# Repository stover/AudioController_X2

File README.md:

# AudioController_X2
RN52 based audio board with ATMega328P and TSOP38238 IR control.

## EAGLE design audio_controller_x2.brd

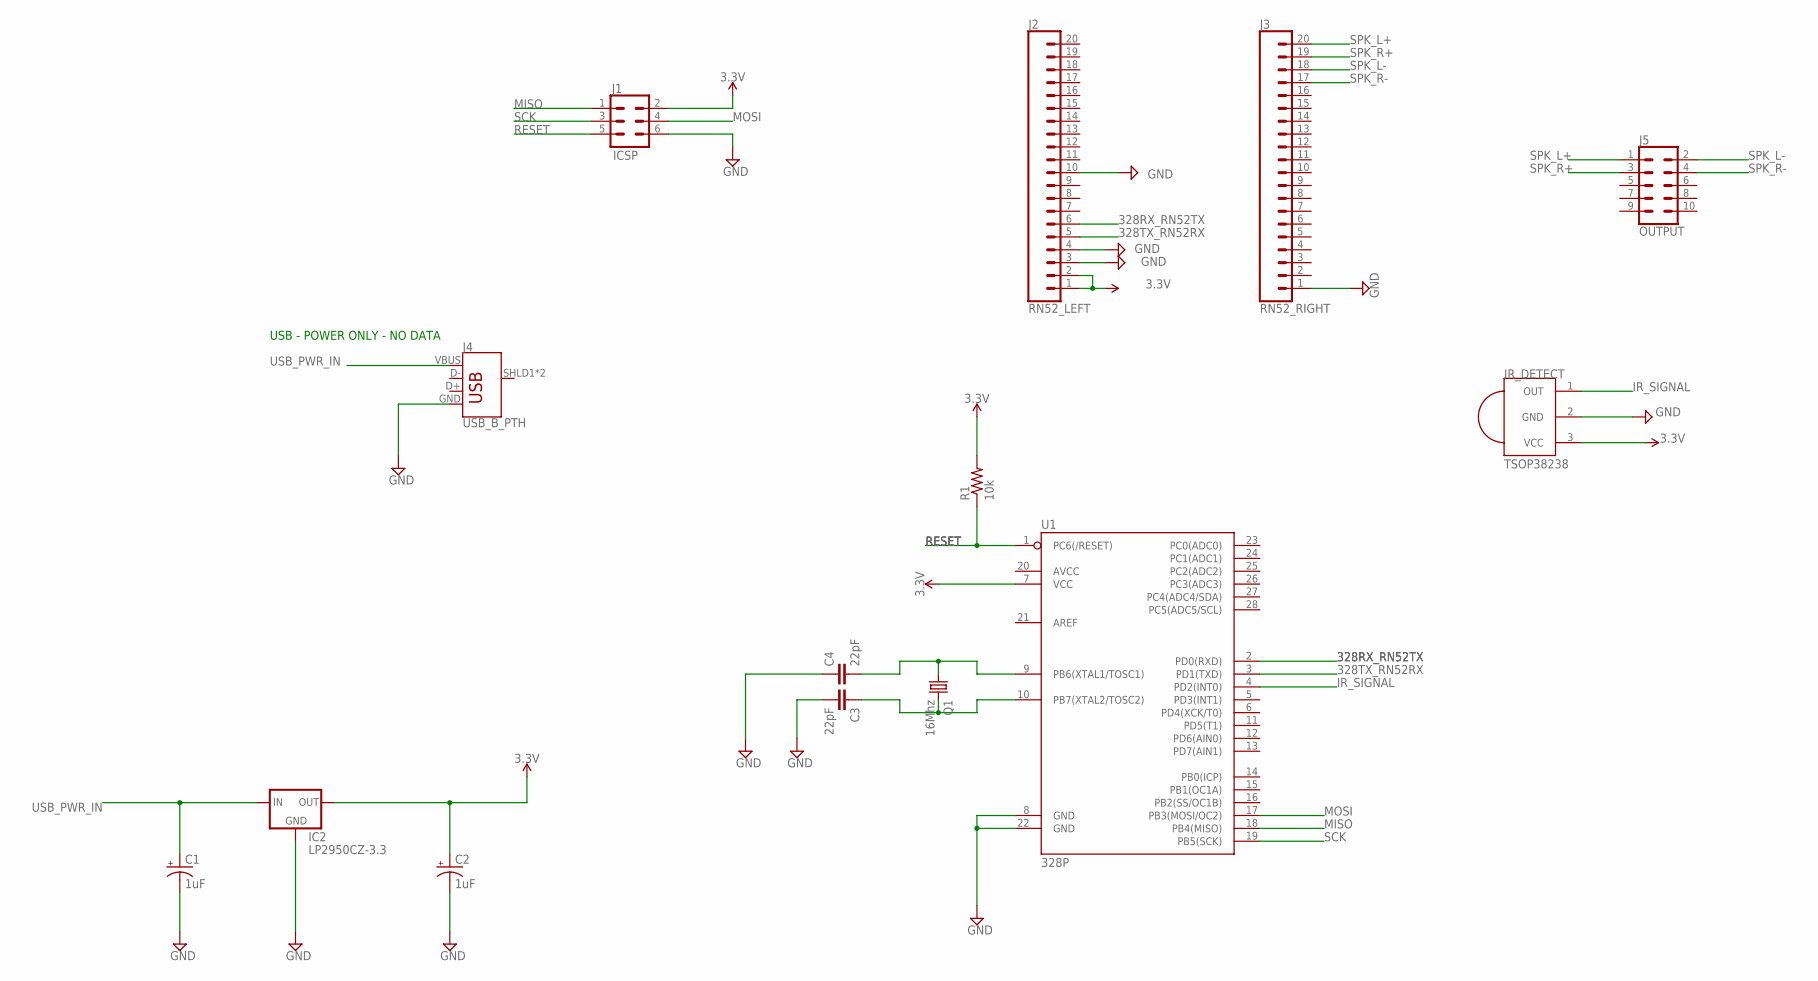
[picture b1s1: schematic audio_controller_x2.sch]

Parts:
C1, C2: 1uF; E2,5-5
C3, C4: 22pF; CAP-PTH-2.54
IC2: LP2950CZ-3.3; TO92
IR_DETECT: TSOP38238; PNA460XM
J1: ICSP; 2X3-SHROUDED
J2: RN52_LEFT; 1X20
J3: RN52_RIGHT; 1X20
J4: USB_B_PTH; USB-B-PTH
J5: OUTPUT; 2X5-SHROUDED
Q1: 16Mhz; HC49/S
R1: 10k; 0207/10
U1: 328P; DIP28

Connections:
3.3V: C2.+, IC2.1 (OUT), IR_DETECT.3 (VCC), J1.2, J2.1, J2.2, R1.2, U1.7 (VCC)
328RX_RN52TX: J2.6, U1.2 (PD0(RXD))
328TX_RN52RX: J2.5, U1.3 (PD1(TXD))
GND: C1.-, C2.-, C3.2, C4.1, IC2.2 (GND), IR_DETECT.2 (GND), J1.6, J2.3, J2.4, J2.10, J3.1, J4.GND, U1.8 (GND), U1.22 (GND)
IR_SIGNAL: IR_DETECT.1 (OUT), U1.4 (PD2(INT0))
MISO: J1.1, U1.18 (PB4(MISO))
MOSI: J1.4, U1.17 (PB3(MOSI/OC2))
unnamed: C4.2, Q1.1, U1.9 (PB6(XTAL1/TOSC1))
unnamed: C3.1, Q1.2, U1.10 (PB7(XTAL2/TOSC2))
RESET: J1.5, R1.1, U1.1 (PC6(/RESET))
SCK: J1.3, U1.19 (PB5(SCK))
SPK_L+: J3.20, J5.1
SPK_L-: J3.18, J5.2
SPK_R+: J3.19, J5.3
SPK_R-: J3.17, J5.4
USB_PWR_IN: C1.+, IC2.3 (IN), J4.VBUS

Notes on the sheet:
USB - POWER ONLY - NO DATA

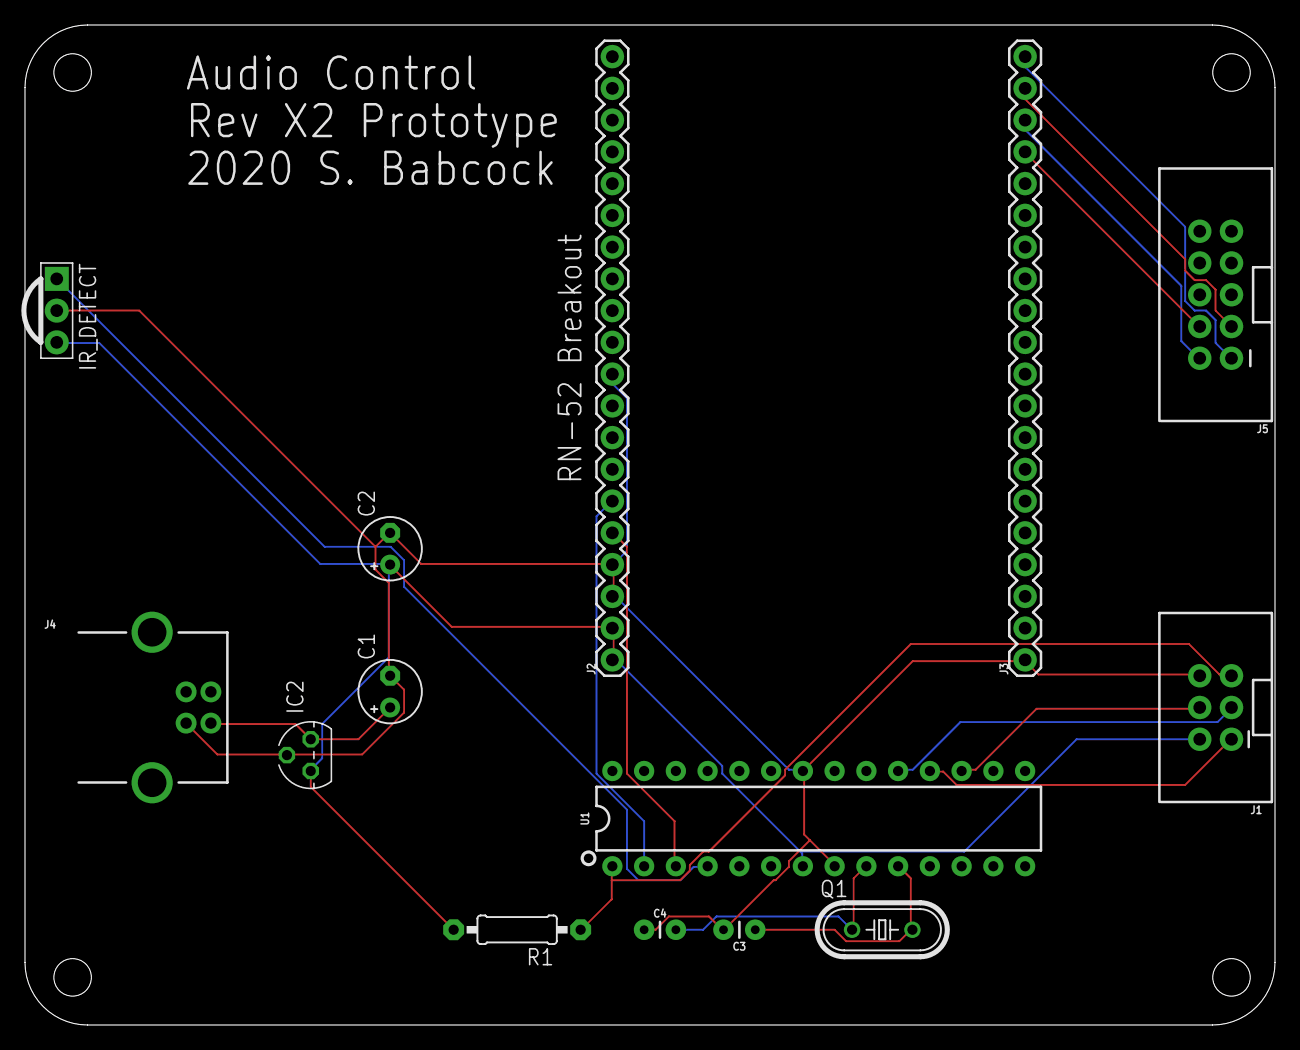
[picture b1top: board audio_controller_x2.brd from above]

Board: 2 copper layers, 100.0 x 80.0 mm, 14 parts (0 on the bottom side), 16 nets.

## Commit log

2020-03-05 Initial add for audio controller board files.
    Initial add for audio controller board files. Eagle schematic and board files. Rev X1/X2 test board.

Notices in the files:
parts and their libraries:
SparkFun-Capacitors: Licensing: Creative Commons ShareAlike 4.0 International - https://creativecommons.org/licenses/by-sa/4.0
